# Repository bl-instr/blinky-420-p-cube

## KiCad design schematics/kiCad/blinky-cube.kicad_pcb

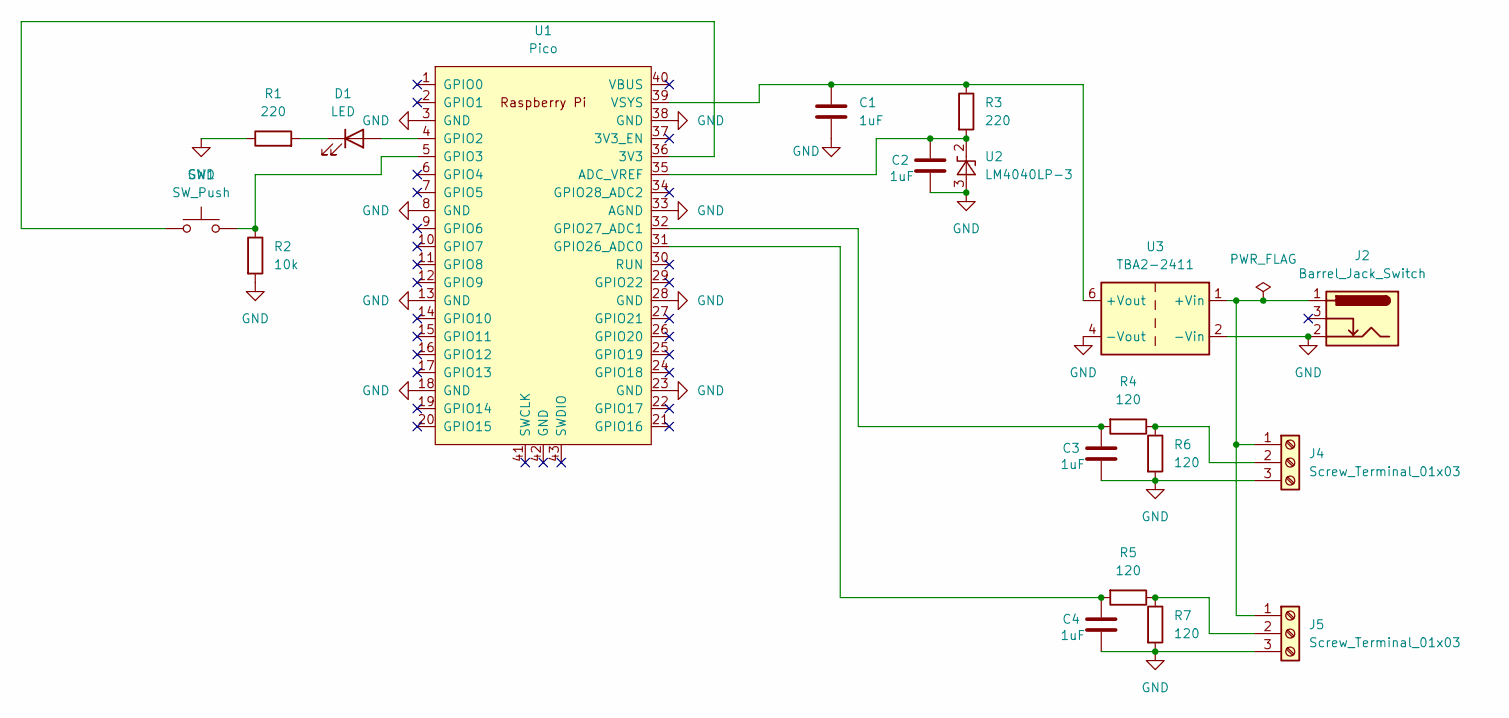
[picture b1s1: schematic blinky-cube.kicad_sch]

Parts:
C1, C2, C3, C4: 1uF; C_Disc_D4.7mm_W2.5mm_P5.00mm
D1: LED; LED_D5.0mm
J2: Barrel_Jack_Switch; BarrelJack_Horizontal
J4, J5: Screw_Terminal_01x03; TerminalBlock_Phoenix_MKDS-3-3-5.08_1x03_P5.08mm_Horizontal
R1, R3: 220; R_Axial_DIN0207_L6.3mm_D2.5mm_P7.62mm_Horizontal
R2: 10k; R_Axial_DIN0207_L6.3mm_D2.5mm_P7.62mm_Horizontal
R4, R5, R6, R7: 120; R_Axial_DIN0207_L6.3mm_D2.5mm_P7.62mm_Horizontal
SW1: SW_Push; SW_PUSH_6mm
U1: Pico; RPi_Pico_SMD_TH
U2: LM4040LP-3; TO-92_Inline
U3: TBA2-2411; Converter_DCDC_TRACO_TBA2-xxxx_Single_THT

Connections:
GND: C1.2, C2.2, C3.2, C4.2, J2.2, J4.3, J5.3, R1.1, R2.2, R6.2, R7.2, U1.3 (GND), U1.8 (GND), U1.13 (GND), U1.18 (GND), U1.23 (GND), U1.28 (GND), U1.33 (AGND), U1.38 (GND), U2.3 (A), U3.2 (-Vin), U3.4 (-Vout)
unnamed: D1.2 (A), U1.4 (GPIO2)
unnamed: D1.1 (K), R1.2
unnamed: J2.1, J4.1, J5.1, U3.1 (+Vin)
unnamed: J4.2, R4.1, R6.1
unnamed: J5.2, R5.1, R7.1
unnamed: SW1.1, U1.36 (3V3)
unnamed: C2.1, R3.2, U1.35 (ADC_VREF), U2.2 (K)
unnamed: R2.1, SW1.2, U1.5 (GPIO3)
unnamed: C4.1, R5.2, U1.31 (GPIO26_ADC0)
unnamed: C3.1, R4.2, U1.32 (GPIO27_ADC1)
unnamed: C1.1, R3.1, U1.39 (VSYS), U3.6 (+Vout)

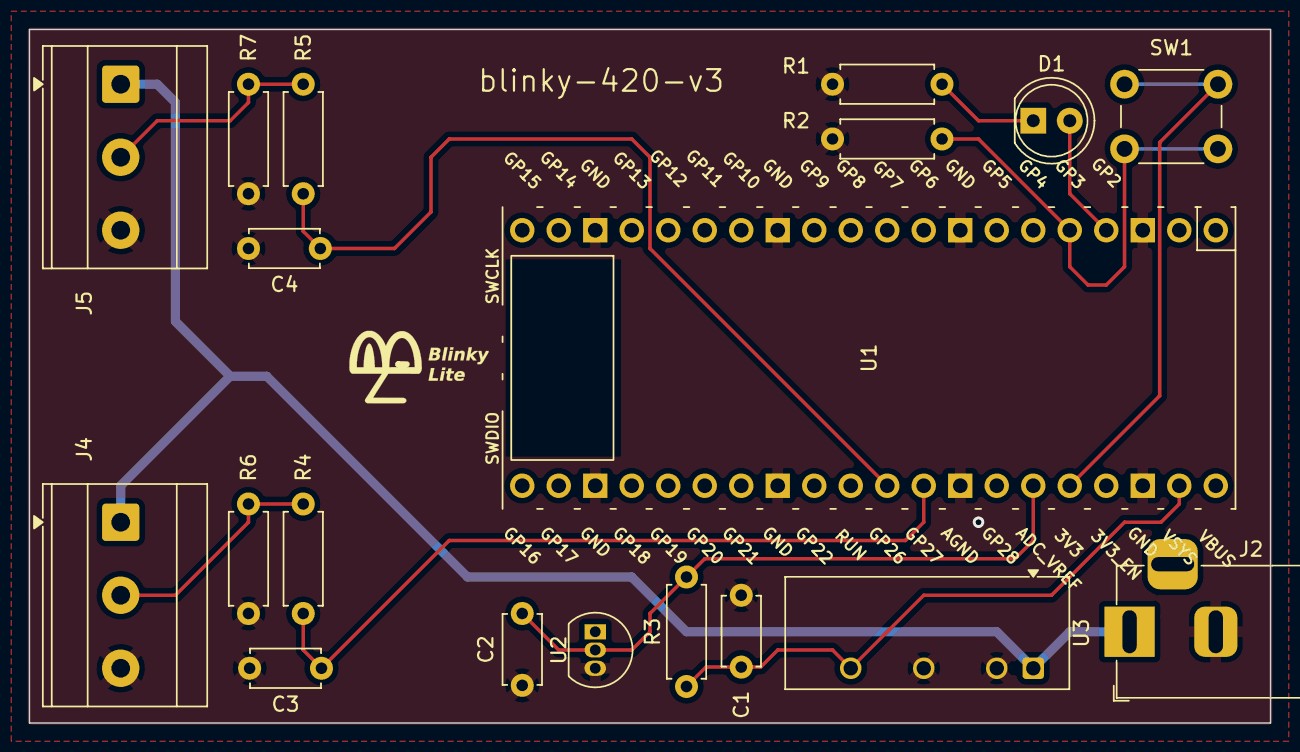
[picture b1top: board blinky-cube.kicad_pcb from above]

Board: 2 copper layers, 86.4 x 48.3 mm, 19 parts (0 on the bottom side), 12 nets.

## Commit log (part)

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2025-02-16 working with picoW
